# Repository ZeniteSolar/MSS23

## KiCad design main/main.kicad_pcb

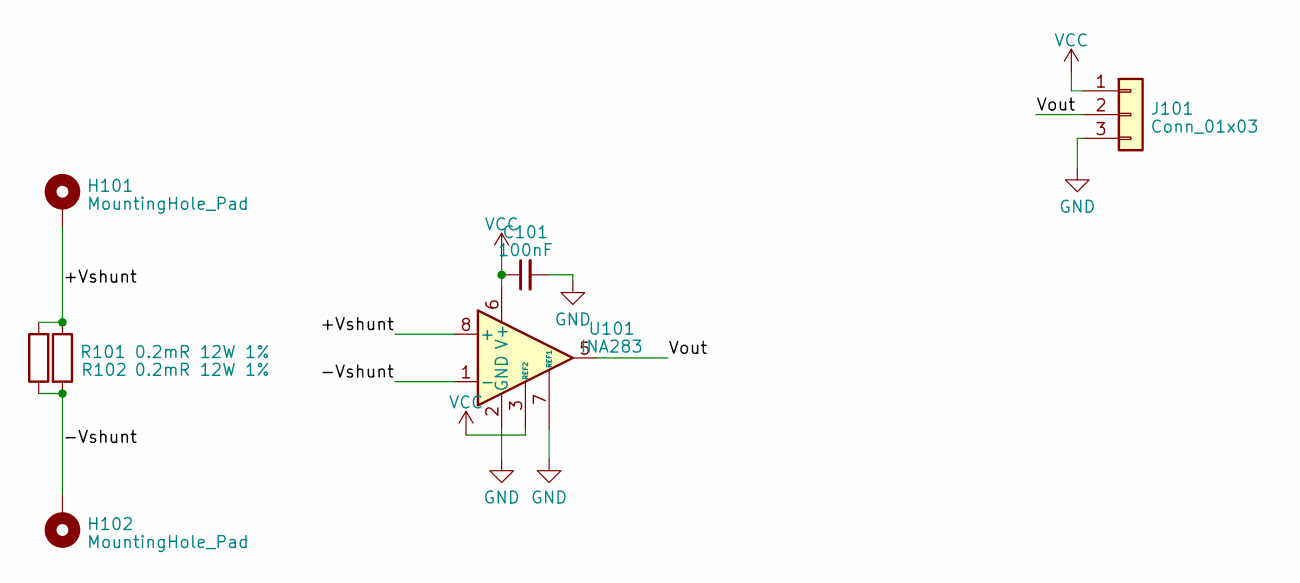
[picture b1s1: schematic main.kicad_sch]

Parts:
C101: 100nF; C_0805_2012Metric_Pad1.18x1.45mm_HandSolder
H101, H102: MountingHole_Pad; MountingHole_13mmx13mm_Rectangular
J101: Conn_01x03; TerminalBlock_bornier-3_P5.08mm
R101, R102: 0.2mR 12W 1%; CSS2H-3920R-L200FE
U101: INA283; SOIC-8_3.9x4.9mm_P1.27mm

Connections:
/+Vshunt: H101.1, R101.1, R102.2, U101.8 (+)
/-Vshunt: H102.1, R101.2, R102.1, U101.1 (-)
/Vout: J101.2, U101.5
GND: C101.2, J101.3, U101.2 (GND), U101.7 (REF1)
VCC: C101.1, J101.1, U101.3 (REF2), U101.6 (V+)

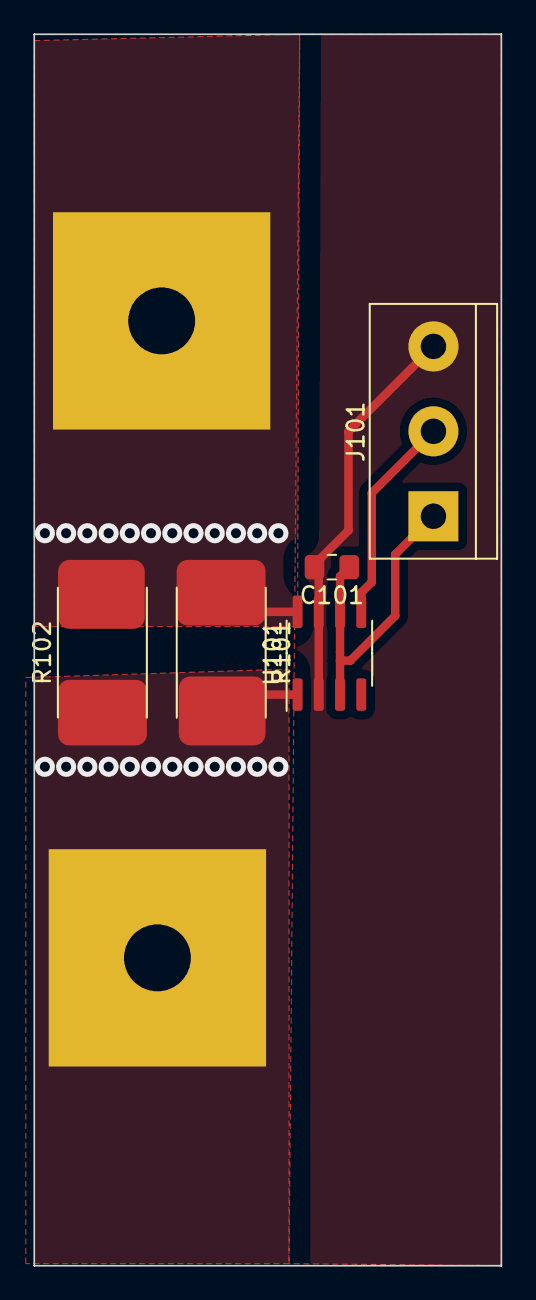
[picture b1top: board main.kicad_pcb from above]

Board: 2 copper layers, 27.9 x 73.7 mm, 7 parts (0 on the bottom side), 5 nets.

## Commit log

2023-04-14 finalize PCB
2023-04-14 create interactive BOM
